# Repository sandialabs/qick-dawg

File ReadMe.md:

# QICK-DAWG

## Quantum Instrumentation Control Kit - <br/>Defect Arbitrary Waveform Generator 

## Description
The Quantum Instrumentation Control Kit - Defect Arbitrary Waveform Generator (QICK-DAWG) is an extension of [QICK](https://github.com/openquantumhardware/qick) with the purpose of controlling nitrogen-vacancy in diamond and other quantum defects for quantum sensing and other quantum applications.  QICK-DAWG utilizes Xilinx Radio Frequency System-on-Chip (RFSoC) Field Programmable Gate Array (FPGAs) evaluation boards which are significantly less expensive than hardware currently available and have the potential for superior capabilities.

In this package we supply specific mw, laser, and readout pulsing code to characterize  photoluminescence intensity, optically detected magnetic resonance (ODMR), spin readout, Rabi Oscillation, Hahn Echo T<sub>2</sub>, and T<sub>1</sub> relaxation. A Jupyter Notebook Demo is included for performing all of these measurements with an RFSoC4x2 to demonstrate typical measurements. 

## Hardware

- [RFSoC4x2](https://www.xilinx.com/support/university/xup-boards/RFSoC4x2.html),   [ZCU111](https://www.xilinx.com/products/boards-and-kits/zcu111.html) and now supporting the [ZCU216](https://www.amd.com/en/products/adaptive-socs-and-fpgas/evaluation-boards/zcu216.html)
- Control Computer
- Router (required if using LAN connection) [(example)](https://www.amazon.com/TP-Link-Integrated-Lightening-Protection-TL-R605/dp/B08QTXNWZ1/ref=asc_df_B08QTXNWZ1/?tag=hyprod-20&linkCode=df0&hvadid=475692076734&hvpos=&hvnetw=g&hvrand=3761702075041011209&hvpone=&hvptwo=&hvqmt=&hvdev=c&hvdvcmdl=&hvlocint=&hvlocphy=1022494&hvtargid=pla-1149738264234&psc=1) and ethernet cords

## Installation
To install QICKDAWG software follow the README found [here](./installation/Readme.md). Software installation includes:
- necessary hardware for the RFSoC4x2, ZCU111 and ZCU216
- cloning QICK-DAWG
- installing necessary packages for the control computer/FPGA
- connecting to the FPGA

## Usage
QICKDAWG has programs for the characterization of:
- Photoluminescence (PL) Intensity
- Optically Detected Magnetic Resonance (ODMR)
- Readout Window
- Rabi Oscillations 
- Hanhn Echo T<sub>2</sub>
- T<sub>1</sub> Relaxation
- Ramsey Interferometry
- Photon counting
- Car-Purcell-Meiboom-Gill (CPMG)

using a ZCU111, RFSoC4x2 and now the ZCU216!

<!-- ### Example use: ###

Optically Detected Magnetic Resonance (ODMR) is one of the QICKDAWG demo pulse sequences. To run ODMR, and any of the other pulse sequences, you must first set the default configuration. The following code, found in the demo Jupyter Notebook, sets the deault configuration.

The following code copies the default configuration, adjusts a a few configuration settings, and runs ODMR. This code is found in the demo Jupyter Notebook. 

The pulse sequencing for ODMR is configured in LockinODMR.py as: 

This is a graph of microwave frequency (MHz) versus ODMR contrast made from data collected using the QICKDAWG ODMR pulse sequencing.

 -->

## Support
To raise an issue use the Issues button on the side bar. Email Andy Mounce at amounce@sandia.gov for further support. 

## Authors and acknowledgment
Andy Mounce<sup>[1](#CINT)</sup>, Emmeline Riendeau<sup>[1](#CINT),[2](#Hav),[3](#Chi)</sup> 

<a name="CINT">1</a>: Center for Integrated Nanotechnology (CINT), Sandia National Laboratories<br>
<a name="Hav">2</a>: Haverford College '24 <br>
<a name="Chi">3</a>: UChicago Physics Graduate Program

Thank you to Sho Uemura at Fermi Labs for helping us edit the QICK firmware. 

## License
MIT License 

Copyright 2023 National Technology & Engineering Solutions of Sandia, LLC (NTESS). Under the terms of Contract DE-NA0003525 with NTESS, the U.S. Government retains certain rights in this software.

Permission is hereby granted, free of charge, to any person obtaining a copy
of this software and associated documentation files (the "Software"), to deal
in the Software without restriction, including without limitation the rights
to use, copy, modify, merge, publish, distribute, sublicense, and/or sell
copies of the Software, and to permit persons to whom the Software is
furnished to do so, subject to the following conditions:

The above copyright notice and this permission notice shall be included in all
copies or substantial portions of the Software.

THE SOFTWARE IS PROVIDED "AS IS", WITHOUT WARRANTY OF ANY KIND,
EXPRESS OR IMPLIED, INCLUDING BUT NOT LIMITED TO THE WARRANTIES OF
MERCHANTABILITY, FITNESS FOR A PARTICULAR PURPOSE AND NONINFRINGEMENT.
IN NO EVENT SHALL THE AUTHORS OR COPYRIGHT HOLDERS BE LIABLE FOR ANY CLAIM,
DAMAGES OR OTHER LIABILITY, WHETHER IN AN ACTION OF CONTRACT, TORT OR
OTHERWISE, ARISING FROM, OUT OF OR IN CONNECTION WITH THE SOFTWARE OR THE USE
OR OTHER DEALINGS IN THE SOFTWARE.

## Project status
QICKDAWG project is active and updates will be added as changes are made.

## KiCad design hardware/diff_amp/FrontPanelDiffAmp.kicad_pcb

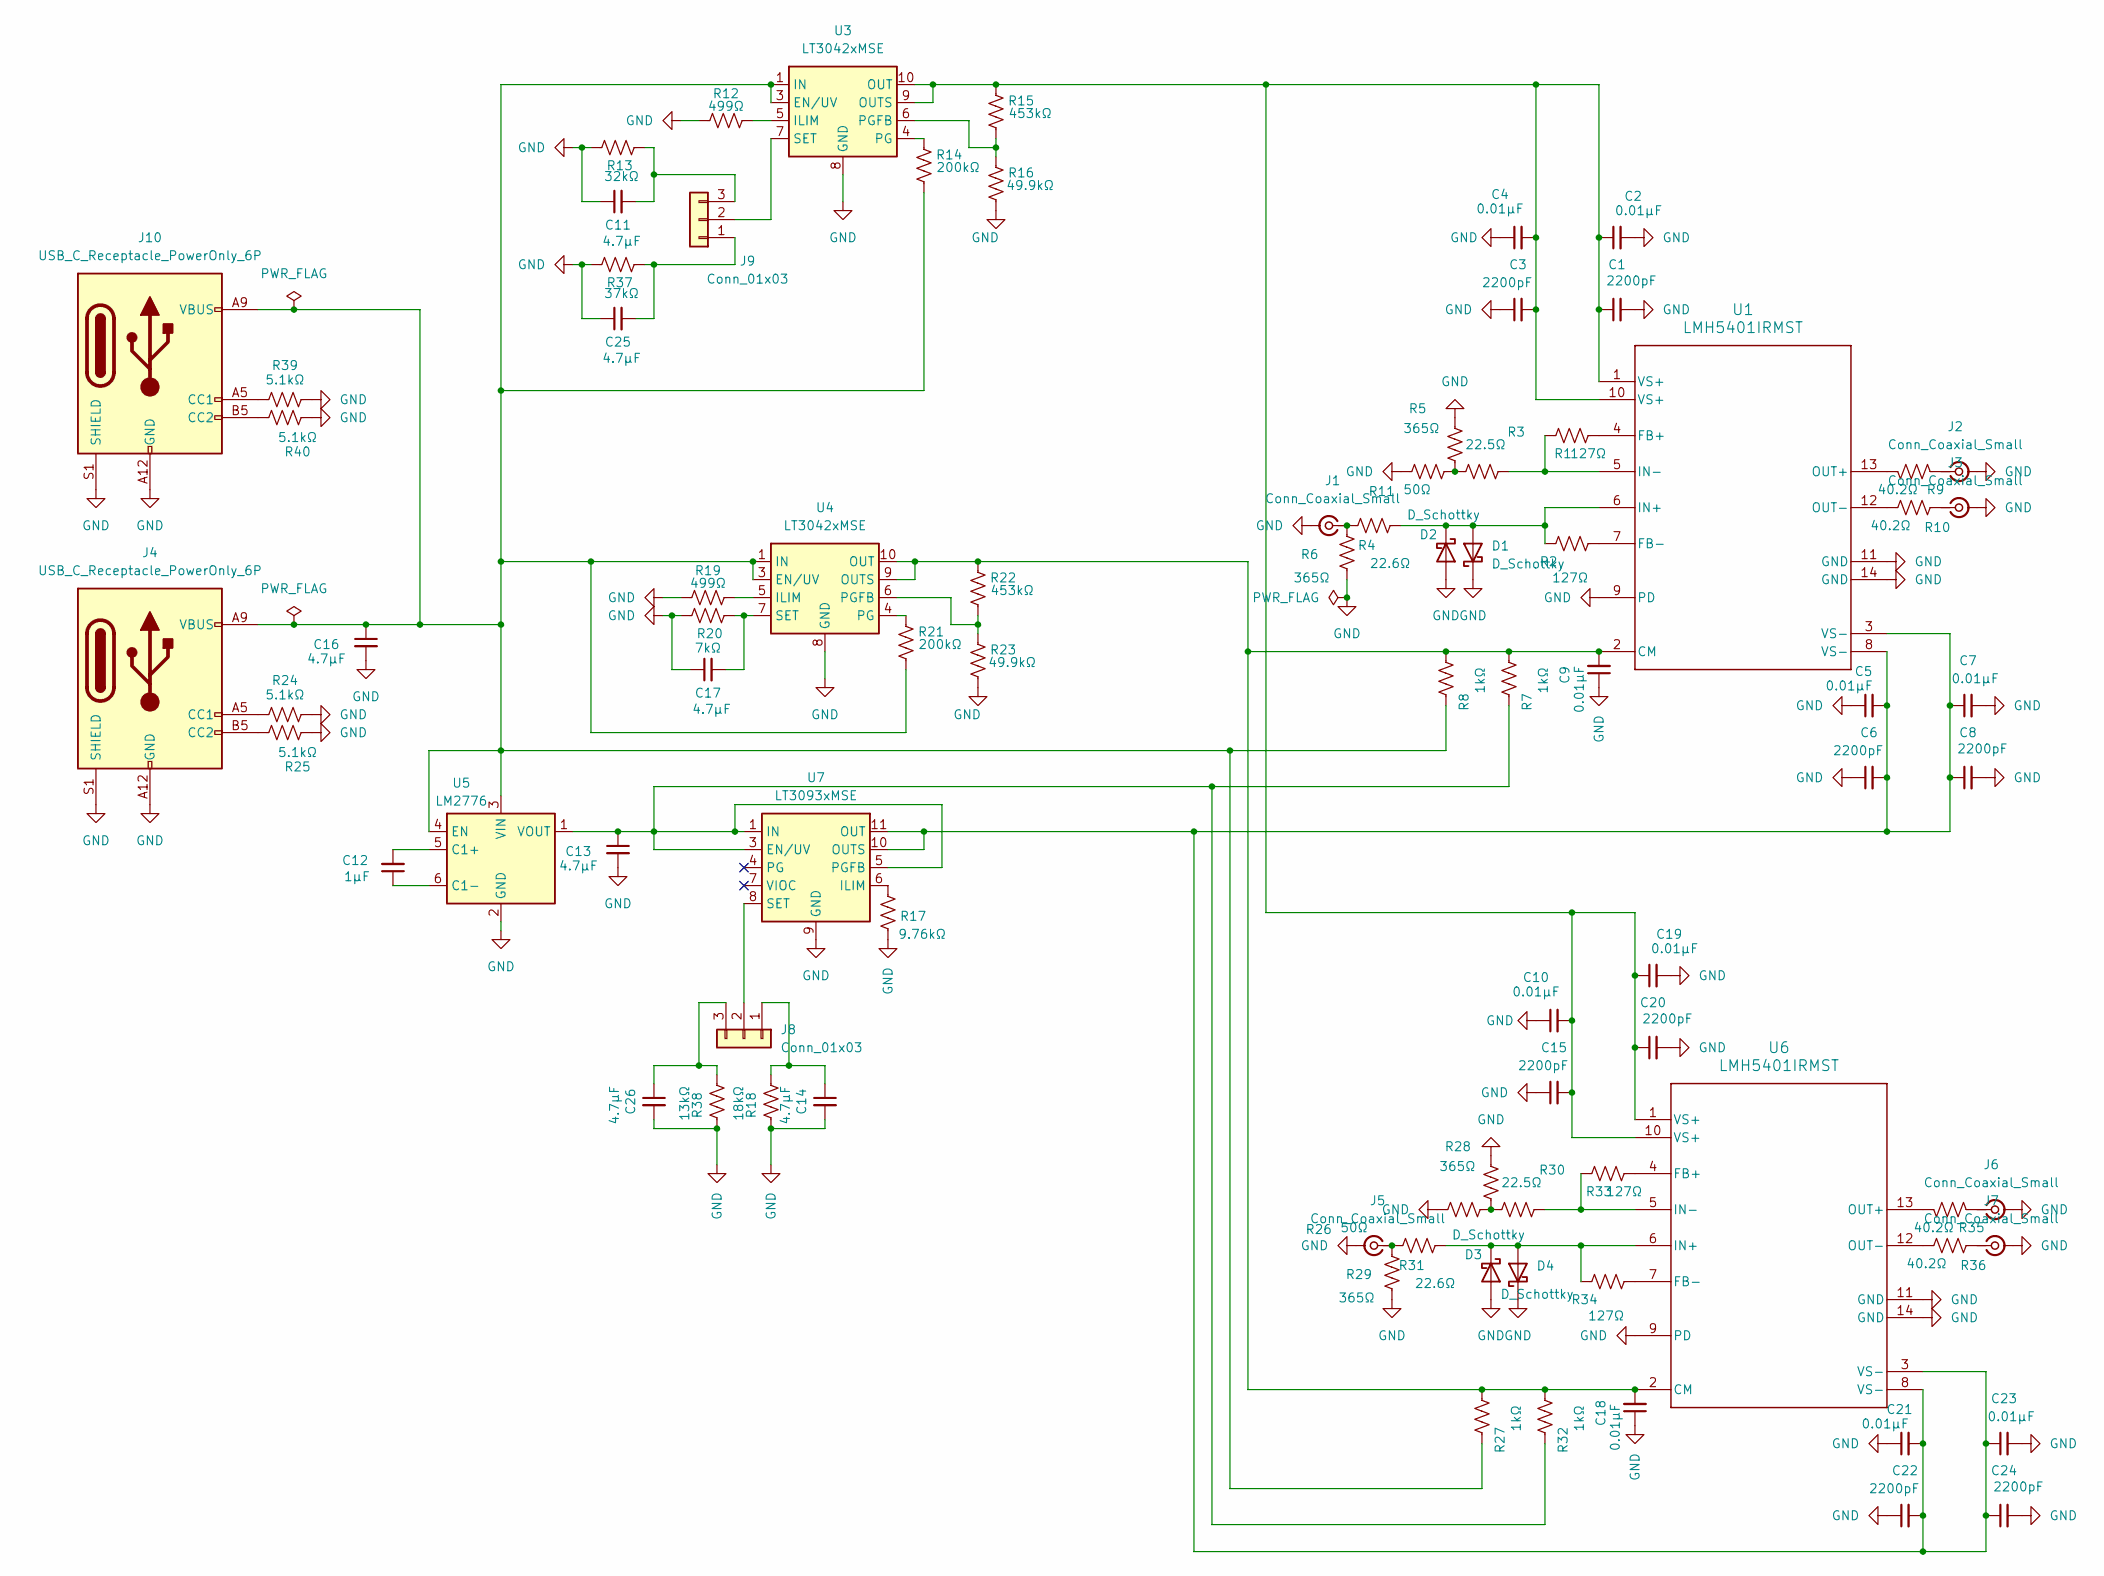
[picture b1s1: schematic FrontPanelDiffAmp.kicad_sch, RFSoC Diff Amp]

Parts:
C1, C3, C6, C8, C15, C20, C22, C24: 2200pF; C_0603_1608Metric
C2, C4, C5, C7, C9, C10, C18, C19, C21, C23: 0.01μF; C_0603_1608Metric
C11, C13, C14, C16, C17, C25, C26: 4.7μF; C_0603_1608Metric
C12: 1μF; C_0603_1608Metric
D1, D2, D3, D4: D_Schottky; D_0402_1005Metric
J1, J5: Conn_Coaxial_Small; SMA_Amphenol_132291-12_Vertical
J2, J3, J6, J7: Conn_Coaxial_Small; SMA_Amphenol_132134-11_Vertical
J4, J10: USB_C_Receptacle_PowerOnly_6P; CUI_UJC-VP-3-SMT-TR
J8, J9: Conn_01x03; PinHeader_1x03_P2.54mm_Vertical
R1, R2, R33, R34: 127Ω; R_0603_1608Metric
R3, R30: 22.5Ω; R_0603_1608Metric
R4, R31: 22.6Ω; R_0603_1608Metric
R5, R6, R28, R29: 365Ω; R_0603_1608Metric
R7, R8, R27, R32: 1kΩ; R_0603_1608Metric
R9, R10, R35, R36: 40.2Ω; R_0603_1608Metric
R11, R26: 50Ω; R_0603_1608Metric
R12, R19: 499Ω; R_0603_1608Metric
R13: 32kΩ; R_0603_1608Metric
R14, R21: 200kΩ; R_0603_1608Metric
R15, R22: 453kΩ; R_0603_1608Metric
R16, R23: 49.9kΩ; R_0603_1608Metric
R17: 9.76kΩ; R_0603_1608Metric
R18: 18kΩ; R_0603_1608Metric
R20: 7kΩ; R_0603_1608Metric
R24, R25, R39, R40: 5.1kΩ; R_0603_1608Metric
R37: 37kΩ; R_0603_1608Metric
R38: 13kΩ; R_0603_1608Metric
U1, U6: LMH5401IRMST; QFN50P250X250X60-14N
U3, U4: LT3042xMSE; MSOP-10-1EP_3x3mm_P0.5mm_EP1.68x1.88mm
U5: LM2776; SOT-23-6
U7: LT3093xMSE; MSOP-12-1EP_3x4.039mm_P0.65mm_EP1.651x2.845mm

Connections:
GND: C1.2, C2.2, C3.1, C4.1, C5.1, C6.1, C7.2, C8.2, C9.1, C10.1, C11.1, C13.2, C14.2, C15.1, C16.2, C17.1, C18.1, C19.2, C20.2, C21.1, C22.1, C23.2, C24.2, C25.1, C26.2, D1.1 (K), D2.2 (A), D3.2 (A), D4.1 (K), J1.2 (Ext), J2.2 (Ext), J3.2 (Ext), J4.A12 (GND), J4.B12 (GND), J4.S1 (SHIELD), J5.2 (Ext), J6.2 (Ext), J7.2 (Ext), J10.A12 (GND), J10.B12 (GND), J10.S1 (SHIELD), R5.2, R6.1, R11.2, R12.1, R13.1, R16.1, R17.1, R18.2, R19.1, R20.1, R23.1, R24.2, R25.1, R26.2, R28.2, R29.1, R37.1, R38.2, R39.2, R40.1, U1.9 (PD), U1.11 (GND), U1.14 (GND), U3.8 (GND), U3.11 (GND), U4.8 (GND), U4.11 (GND), U5.2 (GND), U6.9 (PD), U6.11 (GND), U6.14 (GND), U7.9 (GND)
unnamed: D1.2 (A), D2.1 (K), R2.1, R4.2, U1.6 (IN+)
unnamed: D3.1 (K), D4.2 (A), R31.2, R34.1, U6.6 (IN+)
unnamed: J1.1 (In), R4.1, R6.2
unnamed: J2.1 (In), R9.1
unnamed: J3.1 (In), R10.2
unnamed: J4.A5 (CC1), R24.1
unnamed: J4.B5 (CC2), R25.2
unnamed: J5.1 (In), R29.2, R31.1
unnamed: J6.1 (In), R35.1
unnamed: J7.1 (In), R36.2
unnamed: C14.1, J8.1, R18.1
unnamed: J8.2, U7.8 (SET)
unnamed: C26.1, J8.3, R38.1
unnamed: C25.2, J9.1, R37.2
unnamed: J9.2, U3.7 (SET)
unnamed: C11.2, J9.3, R13.2
unnamed: J10.A5 (CC1), R39.1
unnamed: J10.B5 (CC2), R40.2
unnamed: R3.1, R5.1, R11.1
unnamed: R26.1, R28.1, R30.1
unnamed: C9.2, C18.2, R7.2, R8.2, R22.2, R27.2, R32.2, U1.2 (CM), U4.9 (OUTS), U4.10 (OUT), U6.2 (CM)
unnamed: R1.2, U1.4 (FB+)
unnamed: R2.2, U1.7 (FB-)
unnamed: R1.1, R3.2, U1.5 (IN-)
unnamed: R9.2, U1.13 (OUT+)
unnamed: R10.1, U1.12 (OUT-)
unnamed: C16.1, J4.A9 (VBUS), J4.B9 (VBUS), J10.A9 (VBUS), J10.B9 (VBUS), R8.1, R14.1, R21.1, R27.1, U3.1 (IN), U3.2 (IN), U3.3 (EN/UV), U4.1 (IN), U4.2 (IN), U4.3 (EN/UV), U5.3 (VIN), U5.4 (EN)
unnamed: R12.2, U3.5 (ILIM)
unnamed: C1.1, C2.1, C3.2, C4.2, C10.2, C15.2, C19.1, C20.1, R15.2, U1.1 (VS+), U1.10 (VS+), U3.9 (OUTS), U3.10 (OUT), U6.1 (VS+), U6.10 (VS+)
unnamed: R14.2, U3.4 (PG)
unnamed: R15.1, R16.2, U3.6 (PGFB)
unnamed: R19.2, U4.5 (ILIM)
unnamed: R21.2, U4.4 (PG)
unnamed: R22.1, R23.2, U4.6 (PGFB)
unnamed: C17.2, R20.2, U4.7 (SET)
unnamed: C12.2, U5.5 (C1+)
unnamed: C12.1, U5.6 (C1-)
unnamed: C13.1, R7.1, R32.1, U5.1 (VOUT), U7.1 (IN), U7.2 (IN), U7.3 (EN/UV), U7.5 (PGFB), U7.13 (IN)
unnamed: R33.2, U6.4 (FB+)
unnamed: R34.2, U6.7 (FB-)
unnamed: R30.2, R33.1, U6.5 (IN-)
unnamed: R35.2, U6.13 (OUT+)
unnamed: R36.1, U6.12 (OUT-)
unnamed: R17.2, U7.6 (ILIM)
unnamed: C5.2, C6.2, C7.1, C8.1, C21.2, C22.2, C23.1, C24.1, U1.3 (VS-), U1.8 (VS-), U6.3 (VS-), U6.8 (VS-), U7.10 (OUTS), U7.11 (OUT), U7.12 (OUT)

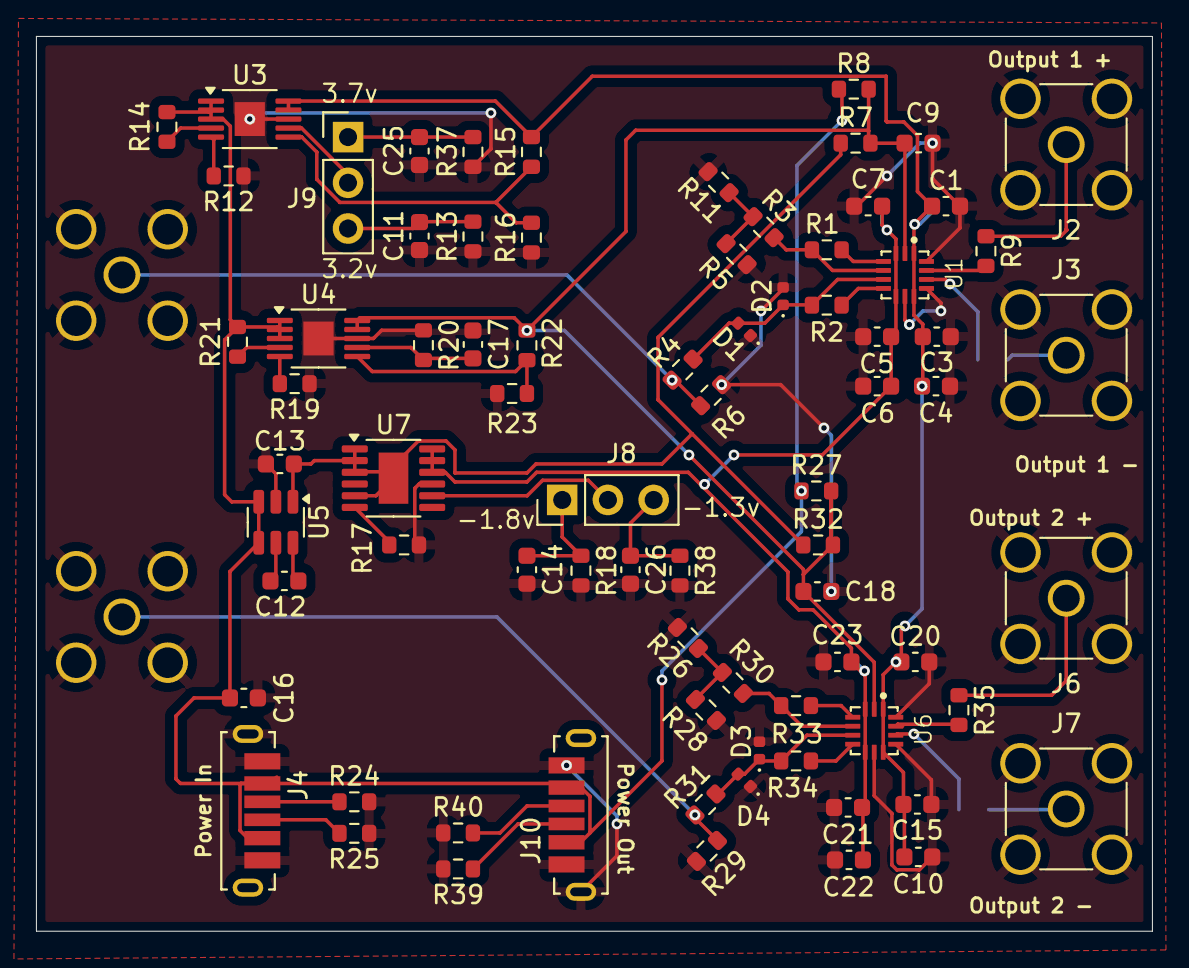
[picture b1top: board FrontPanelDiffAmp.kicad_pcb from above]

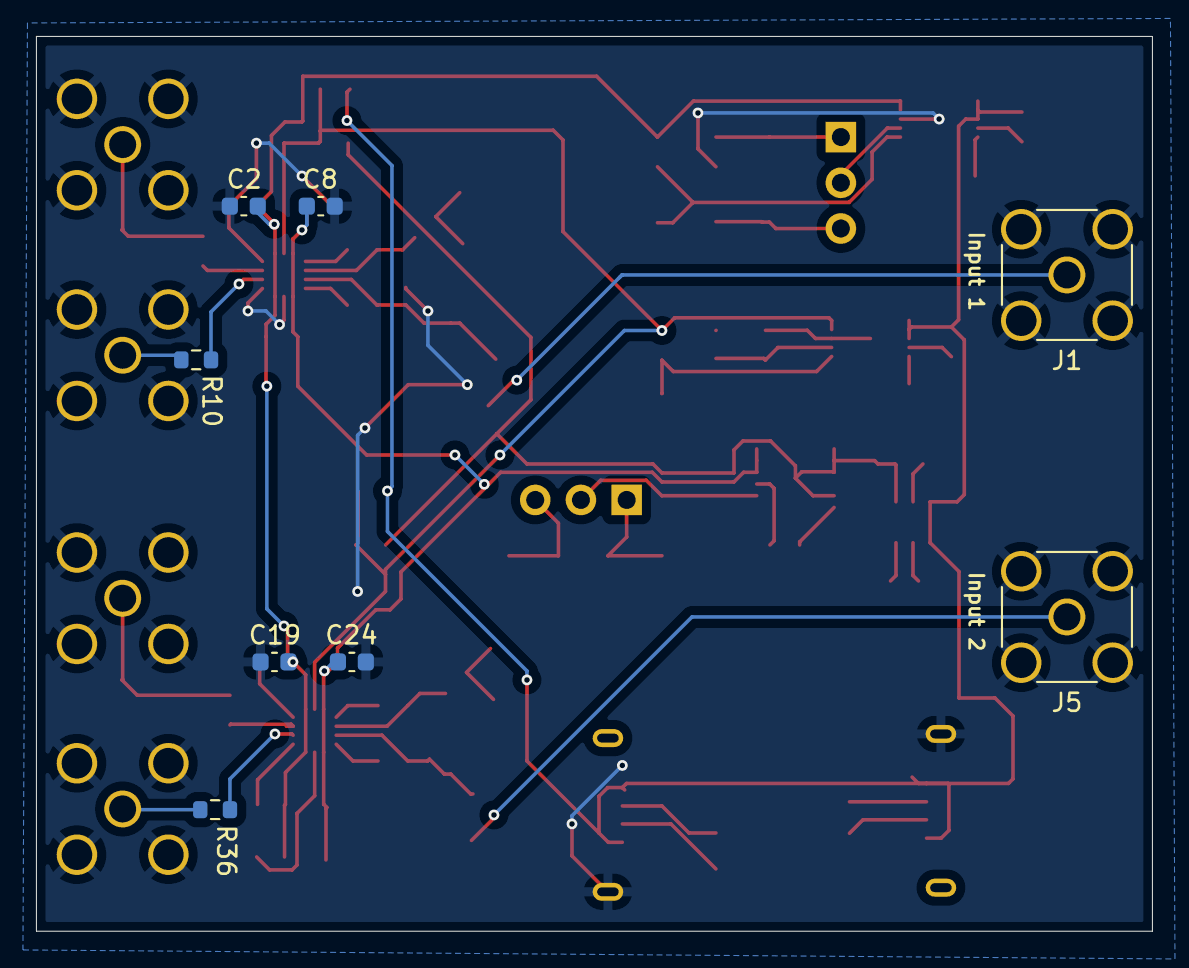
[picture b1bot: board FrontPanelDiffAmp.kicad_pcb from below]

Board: 2 copper layers, 62.0 x 49.7 mm, 86 parts (8 on the bottom side), 46 nets.

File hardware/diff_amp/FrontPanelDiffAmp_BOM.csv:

Id,Designator,Footprint,Quantity,Designation,Supplier and ref
1,"U3,U4",LT3042EMSE#TRPBF,2,LT3042xMSE,
2,"R32,R8,R27,R7",RMCF0603FT1K00,4,1kΩ,
3,"R9,R35,R10,R36",RMCF0603FT40R2,4,40.2Ω,
4,"R19,R12",RMCF0603FT499R,2,499Ω,
5,"J3,J7,J6,J2",SMA_Amphenol_132134-16_Vertical,4,Conn_Coaxial_Small,
6,U5,LM2776DBVR,1,LM2776,
7,"R30,R3",RC0603FR-0722R6L,2,22.5Ω,
8,"C13,C14,C25,C16,C17,C26,C11",CL10A475KP8NNNC,7,4.7μF,
9,"C5,C10,C18,C23,C21,C4,C7,C9,C19,C2",C0603C103K5RACTU,10,0.01μF,
10,"R23,R16",CR0603-FX-4992ELF,2,49.9kΩ,
11,"D4,D3,D1,D2",ACDBQC0130L-HF,4,D_Schottky,
12,"C6,C22,C20,C15,C3,C1,C24,C8",C0603C222K5RACTU,8,2200pF,
13,"R40,R25,R39,R24",RC0603FR-075K1L,4,5.1kΩ,
14,R17,RC0603FR-079K76L,1,9.76kΩ,
15,R37,RN73R1JTTD3702F100,1,37kΩ,
16,R20,ERA-3AEB6981V,1,7kΩ,
17,U7,LT3093EMSE#PBF,1,LT3093xMSE,
18,"R22,R15",ERJ-3EKF4533V,2,453kΩ,
19,R18,RC0603FR-0718KL,1,18kΩ,
20,"R11,R26",CRCW060350R0FKEA,2,50Ω,
21,C12,C0603C104K3RACTU,1,1μF,
22,R13,RN73R1JTTD3202B25,1,32kΩ,
23,"R31,R4",RC0603FR-0722R6L,2,22.6Ω,
24,"R21,R14",RG1608P-204-B-T5,2,200kΩ,
25,R38,RC0603FR-0713KL,1,13kΩ,
26,"J9,J8",61300311121,2,Conn_01x03,
27,"R1,R34,R33,R2",RC0603FR-07127RL,4,127Ω,
28,"J4,J10",USB4140-GF-0170-C,2,USB_C_Receptacle_PowerOnly_6P,
29,"R28,R6,R29,R5",RC0603FR-07365RL,4,365Ω,
30,"U6,U1",LMH5401IRMST,2,LMH5401IRMST,
31,"J1,J5",RF2-152-T-00-50-G-HDW,2,Conn_Coaxial_Large,

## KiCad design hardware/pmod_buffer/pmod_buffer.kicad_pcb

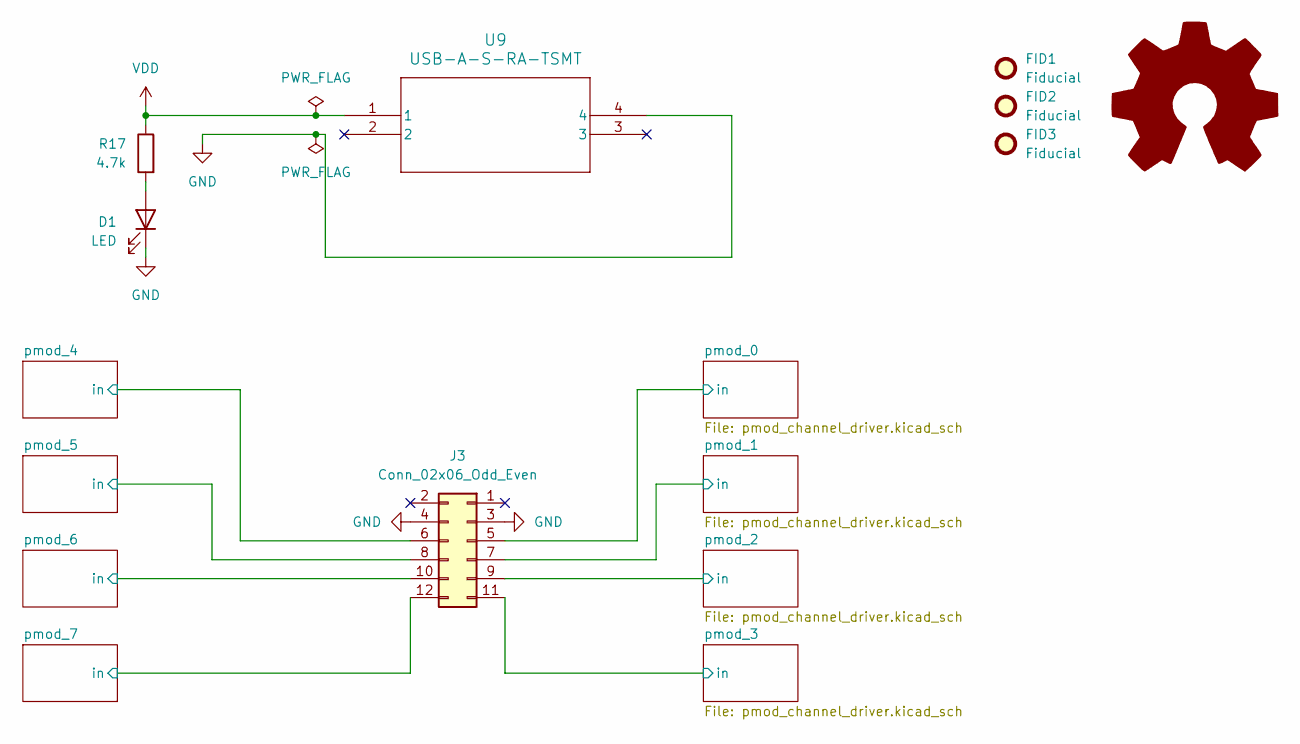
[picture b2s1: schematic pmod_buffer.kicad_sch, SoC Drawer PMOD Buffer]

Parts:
D1: LED; LED_0603_1608Metric
FID1, FID2, FID3: Fiducial; Fiducial_1mm_Mask2mm
J3: Conn_02x06_Odd_Even; PinHeader_2x06_P2.54mm_Vertical
R17: 4.7k; R_0805_2012Metric_Pad1.20x1.40mm_HandSolder
SYM1: Logo_Open_Hardware_Large; OSHW-Logo2_9.8x8mm_SilkScreen
U9: USB-A-S-RA-TSMT; USB-A-S-RA-TSMT_ADM

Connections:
/pmod_0/in: J3.5; also elsewhere on the board
/pmod_1/in: J3.7; also elsewhere on the board
/pmod_2/in: J3.9; also elsewhere on the board
/pmod_3/in: J3.11; also elsewhere on the board
/pmod_4/in: J3.6; also elsewhere on the board
/pmod_5/in: J3.8; also elsewhere on the board
/pmod_6/in: J3.10; also elsewhere on the board
/pmod_7/in: J3.12; also elsewhere on the board
GND: D1.1 (K), J3.3, J3.4, U9.4; also elsewhere on the board
unnamed: D1.2 (A), R17.2
VDD: R17.1, U9.1; also elsewhere on the board

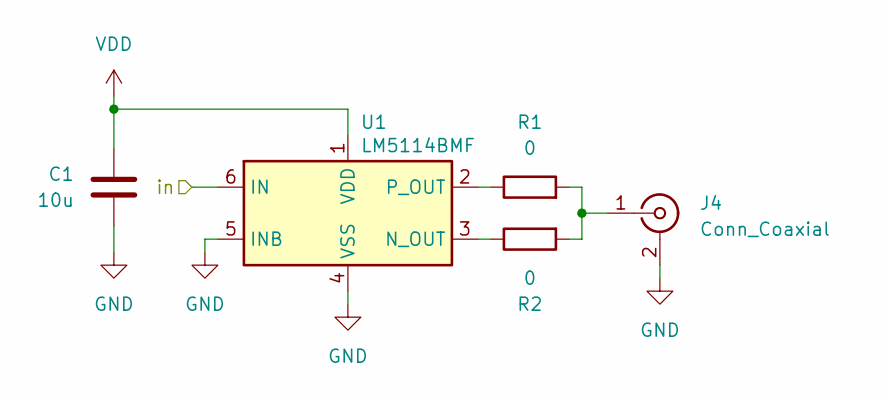
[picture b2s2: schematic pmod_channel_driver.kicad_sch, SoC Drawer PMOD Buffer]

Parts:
C1: 10u; C_0805_2012Metric
J4: Conn_Coaxial; SMA_Amphenol_132134_Vertical
R1, R2: 0; R_0805_2012Metric
U1: LM5114BMF; SOT-23-6

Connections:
/pmod_0/in: U1.6 (IN); also elsewhere on the board
GND: C1.2, J4.2 (Ext), U1.4 (VSS), U1.5 (INB); also elsewhere on the board
unnamed: J4.1 (In), R1.2, R2.2
unnamed: R2.1, U1.3 (N_OUT)
unnamed: R1.1, U1.2 (P_OUT)
VDD: C1.1, U1.1 (VDD); also elsewhere on the board

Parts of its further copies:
C2, C3, C4, C5, C6, C7, C8: 10u; C_0805_2012Metric
J5, J6, J7, J8, J9, J10, J11: Conn_Coaxial; SMA_Amphenol_132134_Vertical
R3, R4, R5, R6, R7, R8, R9, R10, R11, R12, R13, R14, R15, R16: 0; R_0805_2012Metric
U2, U3, U4, U5, U6, U7, U8: LM5114BMF; SOT-23-6

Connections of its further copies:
/pmod_1/in: U2.6 (IN); also elsewhere on the board
/pmod_2/in: U3.6 (IN); also elsewhere on the board
/pmod_3/in: U4.6 (IN); also elsewhere on the board
/pmod_4/in: U5.6 (IN); also elsewhere on the board
/pmod_5/in: U6.6 (IN); also elsewhere on the board
/pmod_6/in: U7.6 (IN); also elsewhere on the board
/pmod_7/in: U8.6 (IN); also elsewhere on the board
GND: C2.2, C3.2, C4.2, C5.2, C6.2, C7.2, C8.2, J5.2 (Ext), J6.2 (Ext), J7.2 (Ext), J8.2 (Ext), J9.2 (Ext), J10.2 (Ext), J11.2 (Ext), U2.4 (VSS), U2.5 (INB), U3.4 (VSS), U3.5 (INB), U4.4 (VSS), U4.5 (INB), U5.4 (VSS), U5.5 (INB), U6.4 (VSS), U6.5 (INB), U7.4 (VSS), U7.5 (INB), U8.4 (VSS), U8.5 (INB); also elsewhere on the board
unnamed: J5.1 (In), R3.2, R4.2
unnamed: J6.1 (In), R5.2, R6.2
unnamed: J7.1 (In), R7.2, R8.2
unnamed: J8.1 (In), R9.2, R10.2
unnamed: J9.1 (In), R11.2, R12.2
unnamed: J10.1 (In), R13.2, R14.2
unnamed: J11.1 (In), R15.2, R16.2
unnamed: R4.1, U2.3 (N_OUT)
unnamed: R3.1, U2.2 (P_OUT)
unnamed: R6.1, U3.3 (N_OUT)
unnamed: R5.1, U3.2 (P_OUT)
unnamed: R8.1, U4.3 (N_OUT)
unnamed: R7.1, U4.2 (P_OUT)
unnamed: R10.1, U5.3 (N_OUT)
unnamed: R9.1, U5.2 (P_OUT)
unnamed: R12.1, U6.3 (N_OUT)
unnamed: R11.1, U6.2 (P_OUT)
unnamed: R14.1, U7.3 (N_OUT)
unnamed: R13.1, U7.2 (P_OUT)
unnamed: R16.1, U8.3 (N_OUT)
unnamed: R15.1, U8.2 (P_OUT)
VDD: C2.1, C3.1, C4.1, C5.1, C6.1, C7.1, C8.1, U2.1 (VDD), U3.1 (VDD), U4.1 (VDD), U5.1 (VDD), U6.1 (VDD), U7.1 (VDD), U8.1 (VDD); also elsewhere on the board

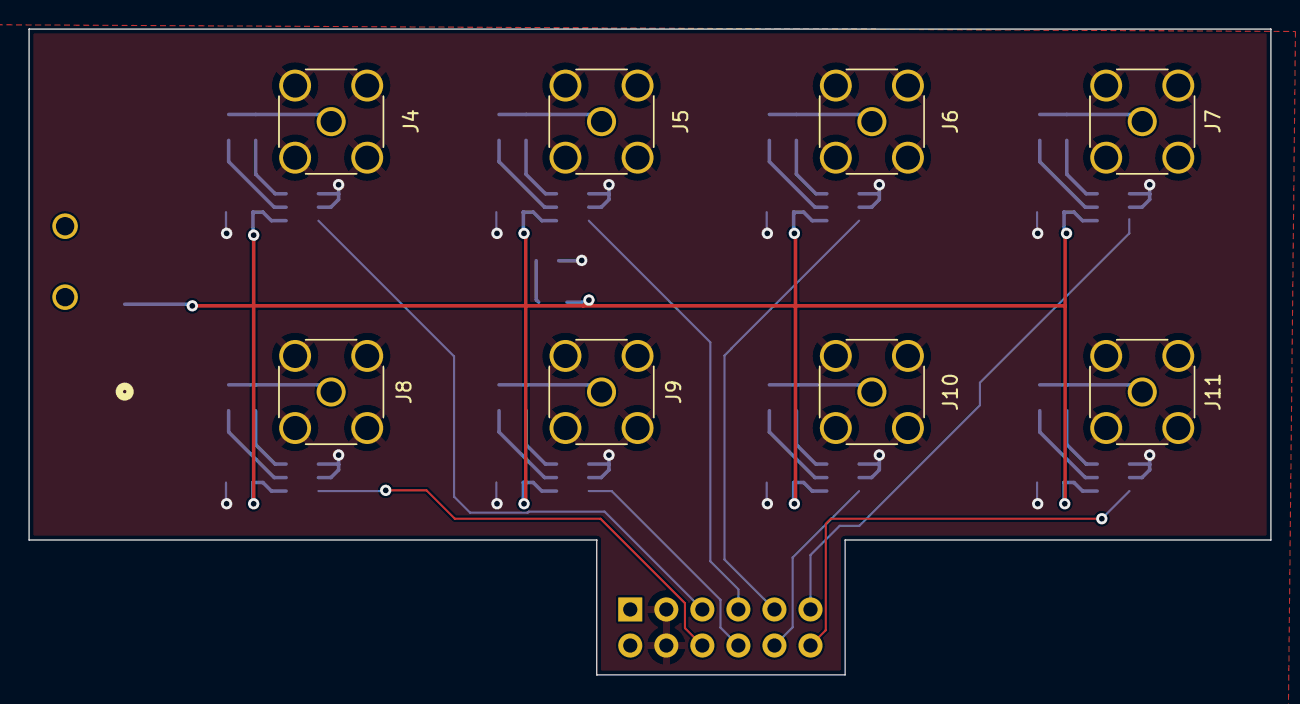
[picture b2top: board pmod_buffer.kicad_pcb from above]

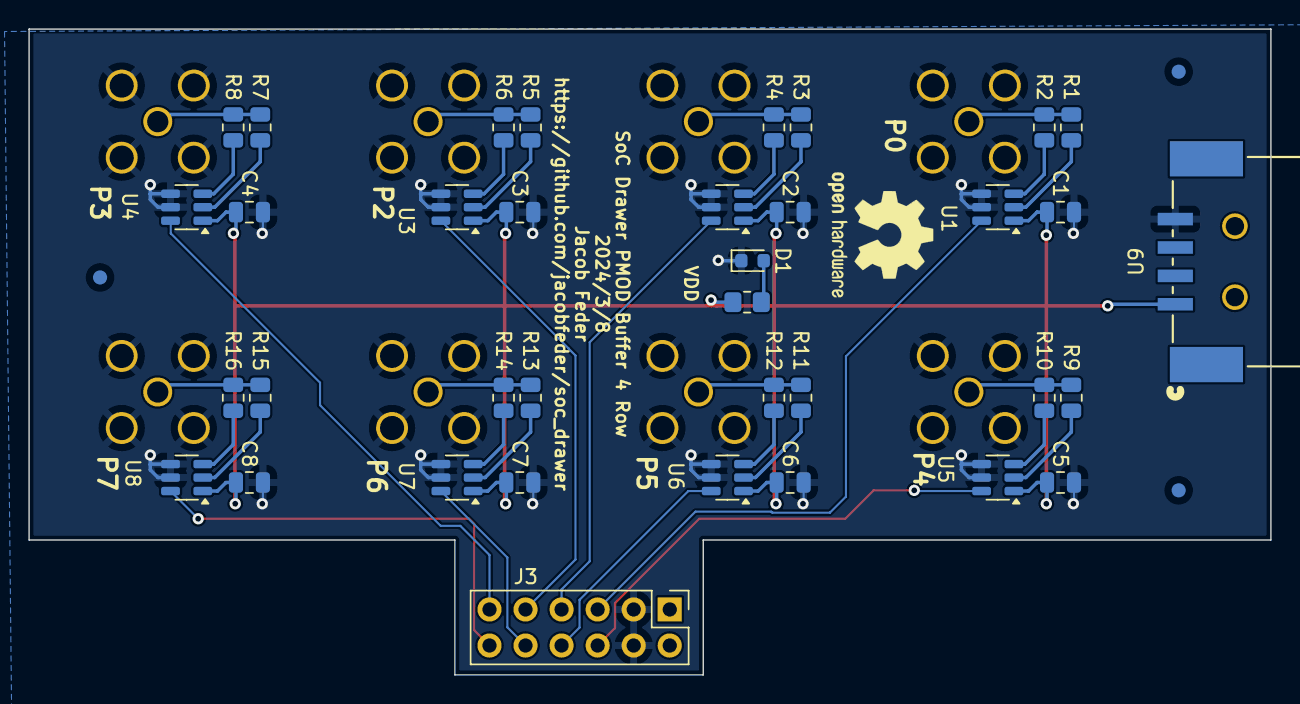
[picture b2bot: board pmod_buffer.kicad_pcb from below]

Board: 2 copper layers, 87.5 x 45.5 mm, 48 parts (40 on the bottom side), 35 nets.

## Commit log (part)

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2023-11-17 Added all of the base files from the Sandia repository.
2023-11-28 paper
2023-11-28 Rename README.md to paper.md
2023-11-28 Rename paper/paper.bib to paper.bib
2023-11-28 Rename paper/paper.md to paper.md
2023-11-30 Added flake8 and linted our current code
2023-12-05 autopep8 with E101,E123,E124,E127,E128,E202,E203,E222,E225,E226,E265,E231,E241,E251,E261,E302,E303,E402,W292,W391
2023-12-05 Full autopep8
2023-12-05 Fixed lines that were too long
2023-12-05 Ignoring complexity for now
2024-01-09 Updating Plot
2024-01-09 started the documetatino for rtd
2024-01-28 replaced setup.py with pyproject.toml
2024-01-28 Self explanitoryy
2024-01-28 Configured docs for read the docs upload
2024-02-06 revised paper
2024-02-07 sourcing graphics
2024-02-07 fixing graphics source issue
2024-02-07 Update index.rst
    Ramsay to Ramsey
2024-02-14 small paper edits
2024-02-21 fixing ramsay to ramsey and adding hardware readme V1
2024-02-21 adding pictures to programs
2024-02-21 upadtes
2024-03-05 pyproject.toml: don't exclude qickdawg package
    - "qick*" excludes the qickdawg package which should be installed
2024-03-19 Readme typos fix
2024-03-20 DEER V1
2024-03-20 logo fix
2024-03-20 gitignore
2024-03-27 adding deer
2024-04-24 logo only issue
2024-04-24 adding labels to images
2024-04-24 trying to fix path
2024-04-24 testing
2024-04-24 jupyter notebook(s)
2024-05-01 fixing logo
2024-05-01 fixing logo take 2
2024-05-01 fixing logo take 3
2024-05-01 revising the installation readme
2024-05-01 revising the installation readme typos
2024-05-01 revising hardware readme
2024-05-01 logo
2024-05-08 updating readme capacitor instructions
2024-05-29 CPMG update
2024-05-29 CPMGXY8 update
2024-05-29 adding cpmg xy 8 n
2024-05-29 cpmg xy8
2024-05-29 writing cpmg xy n
2024-05-31 updating CPMG
2024-05-31 adding qick loop
2024-06-06 fixing my email in toml and fixing the demo so it doesn't say pyscan
2024-06-07 small changed to the demo
2024-06-07 adding jupyter notebook for wifi installation
2024-06-10 updating the readmes
2024-06-14 updating WAN readme
2024-06-14 fixing any hard coded adc channels
2024-06-14 updating readme images
2024-06-24 fixing hard coded adc channel
2024-06-24 updating readme
2024-06-24 updating readme source
2024-06-24 testing yaml file
2024-06-24 removing test yaml file
2024-06-24 copy editing readmes
2024-06-24 copy edits to the readmes
2024-06-24 updating image
2024-06-24 updating picture
2024-06-24 fixing missing /
2024-09-26 added ignore to test.ipynb
2024-09-26 Deleted local QICK, updated qick to 2.287 in requirements
2024-09-27 fix: started to fix NVAverager Program
2024-10-09 fix(upgrade qick): upgraded to qick 0.2.289. BREAKING CHANGE
2024-10-09 fix(init): updated init message
2024-10-09 meta: ignoring test.ipynb
2024-10-09 fix(meta): changed convetional commits and corrected errors for autotesting:
2024-10-09 fix(pyproject): fixed missing quote
2024-10-09 install: fixing pyproject.toml
2024-10-09 chore: added src file to standarize package location
2024-10-09 test: fixed flake8 syntax
2024-10-09 Conventional change log (#45) [skip ci]
2024-10-12 fix(meta): fixed import so it's no longer broken
2024-10-12 fix(meta): fixed import so it's no longer broken (#47) [skip ci]
2024-11-19 feat(): added simple read out window to calibrate photon ttl levels
2024-11-19 feat(): updated laser on/off to read out single TTLs from edge counting mode
2024-11-19 feat(): added NVAverageprogram.setup_readout to setup analog or digital readout
2024-11-19 feat(): PLIntensity now works with edge counting, analysis can be rate or total
2024-11-19 feat(): Lockin-ODMR now has counting mode and analyze digital or analog
2024-11-21 integrating counted rabi
2024-12-04 test new analysis format
2024-12-18 fix(rabi): fixed rabi sequence, dropped 'length' syntax
2024-12-18 fix(pulse_readout): pulse readout end was slightly off
2024-12-18 test(readout): ensures that readout does not extend past laser_on time
2024-12-18 fix(readoutwindow): modified readoutwindow so that it doesn't use sycnall
2024-12-18 Fix (#48) [skip ci]
2024-12-21 chore(reorg): reorganizing files for easier implementation
2025-01-07 feat(client): Added local mode to start client
2025-01-07 fix(itemattribute): used pypi itemattribute with correct item assignment
2025-01-07 feat(cpmgxy8): Added cpmgxy8, delay sweep demonstrated
2025-01-07 fix(pulsing): small pulsing changes with integrated ddr4 and testing
2025-01-07 test(): Added local_nvconfig testing
2025-01-07 test(): added testing notebooks with loopback for ttl and mw
2025-01-07 fix(): updated qick version requirement to include remote fix
2025-01-07 test(): added test notebooks for loopback
2025-01-07 fix(client): fixed start client for remote use
2025-01-07 fix(graphics): fixed the graphics path error
2025-01-07 fix(installation): simplified package installation, only supporting online installs
2025-01-07 including qick_daemon
2025-01-08 reorg(test)
2025-01-08 test(): created remote tests for partial loopback
2025-01-08 progress
2025-01-09 Added counting notebook
2025-01-09 fix(): fixing integration of photon counting with newest version
2025-01-15 fix(install): added itemattribute to the requirements list
2025-01-15 cleanup(): using setup_readout method
2025-01-15 fix(t1): swapped pulsing order for consistent analysis
2025-01-15 fix(): changed analysis to consistently have contrast as just the difference
2025-01-15 update(): updated qickdawg analog notebook with clean run and modern syntax
2025-01-15 Test (#49) [skip ci]
2025-01-17 feat(photon_counting): confirmed photon counting works for all pulse sequences
2025-01-17 syntax(): fixed python sytnax
2025-01-17 Photon counting (#50)
    Added photon counting and tested for all pulse sequences except for
    CPMGXY8-n
    Added DarkCounts program
    Added check_readout function [skip ci]
2025-01-17 docs(): cleaned up and updated documentation for installation
2025-01-17 docs(): fixed some docs issues
2025-01-29 fix(): fixed installation to remove qd install and paths
2025-01-29 fix(): fixed installation to remove qd install and paths (#53) [skip ci]
2025-04-21 firmware: added ZCU111 photon counting firmware
2025-04-25 firmware: added 9ghz firmware for 4x2
2025-07-07 Added hardware folder and pmod board
2025-07-07 added kicad_pro_file
2025-07-16 Create qick_zcu216
2025-07-18 Updated nvaverageprogram.py
2025-07-23 Add photon counting firmware for zcu216
2025-07-23 Add photon counting firmware for the zcu216
2025-07-23 Removed random zcu216 file
2025-07-23 Remove improperly configured submodule zcu216_photon_counting
2025-07-23 Photon counting firmware for zcu216
2025-07-29 zcu216 firmware with new photon counting
2025-07-30 zcu216 firmware source files
2025-07-30 removed 9ghz and qick_111_ADC45 files
2025-07-30 Removed common clk and photon counting files from this branch
2025-07-30 zcu111 firmware coming soon
2025-07-30 4x2 firmware coming soon
2025-10-30 Add enclosures for ZCU111/ZCU216, replace 4x2 enclosure. Add diff_amp CPCB KiCad project
2025-11-05 Fixed ZCU216 Dawg House bottom mounting holes
2026-04-20 build: ZCU216 common clock firmware with 9.5GHz on the DAC. The DAC runs 2x faster than the ADC and tprocessor.
2026-06-01 build: 4x2 firmware with 9.8GHz DAC speed. The DAC runs 2x faster than the ADC and tprocessor.
2026-06-01 ci: Double pulse length if DAC is 2x times faster than the tproc and ADC.
2026-06-04 chore: remove photon counting and unsynced clock firmware
2026-06-04 build: Add zcu111 common clock firmware and build source files.
2026-06-04 build: Add RFSoc4x2 common clock and 2x DAC speed common clock firmware with build source files.
2026-06-04 build: Add zcu216 common clock and 2x DAC speed common clock firmware.
2026-06-04 chore: Add hdl source files from QICK
2026-06-04 chore: Add axis_avg_buffer IP file with edge counting
2026-06-04 chore: Add source directory
2026-06-04 docs: Add README file
2026-06-04 Update README.md
    More changes to come.
2026-06-12 build: zcu111 common clock firmware. All clocks synced at 409.6MHz
2026-06-12 chore: remove unsynced build source files
2026-06-12 build: Add new zcu111 common clock build source files
2026-06-12 Rename bd_2023.1_v2.tcl to bd_2023-1_v2.tcl
2026-06-12 chore: remove unsycned clock firmware build files
2026-06-12 build: Add zcu216 2X DAC-speed common clock build source files
2026-06-15 Update README.md
    Just trying to make the readme look nice.
2026-06-15 Update README.md
    Fixed grammar errors.
2026-06-30 build: Add RFSoc4x2 common firmware. Rename to qickdawg_4x2.bit.
    Rename qickdawg_4x2_commonClk.bit to qickdawg_4x2.bit.
2026-06-30 build: Add RFSoc4x2 common firmware. Rename to qickdawg_4x2.bit
2026-06-30 build: Add zcu216 common firmware. Rename to qickdawg_216.bit
2026-06-30 build: Add zcu216 common firmware. Rename to qickdawg_216.hwh
2026-06-30 build: Rename to to qickdawg_111. ZCU111 common firmware. All clocks synced at 409.6MHz
2026-06-30 build: Rename to qickdawg_111. ZCU111 common firmware. All clocks synced at 409.6MHz
2026-06-30 Update README.md
    Just fixing typos..
2026-06-30 chore: Add zcu111 label picture
2026-06-30 Update zcu111 and zcu216 board labels
2026-06-30 chore: Update zcu111 and zcu216 labels
